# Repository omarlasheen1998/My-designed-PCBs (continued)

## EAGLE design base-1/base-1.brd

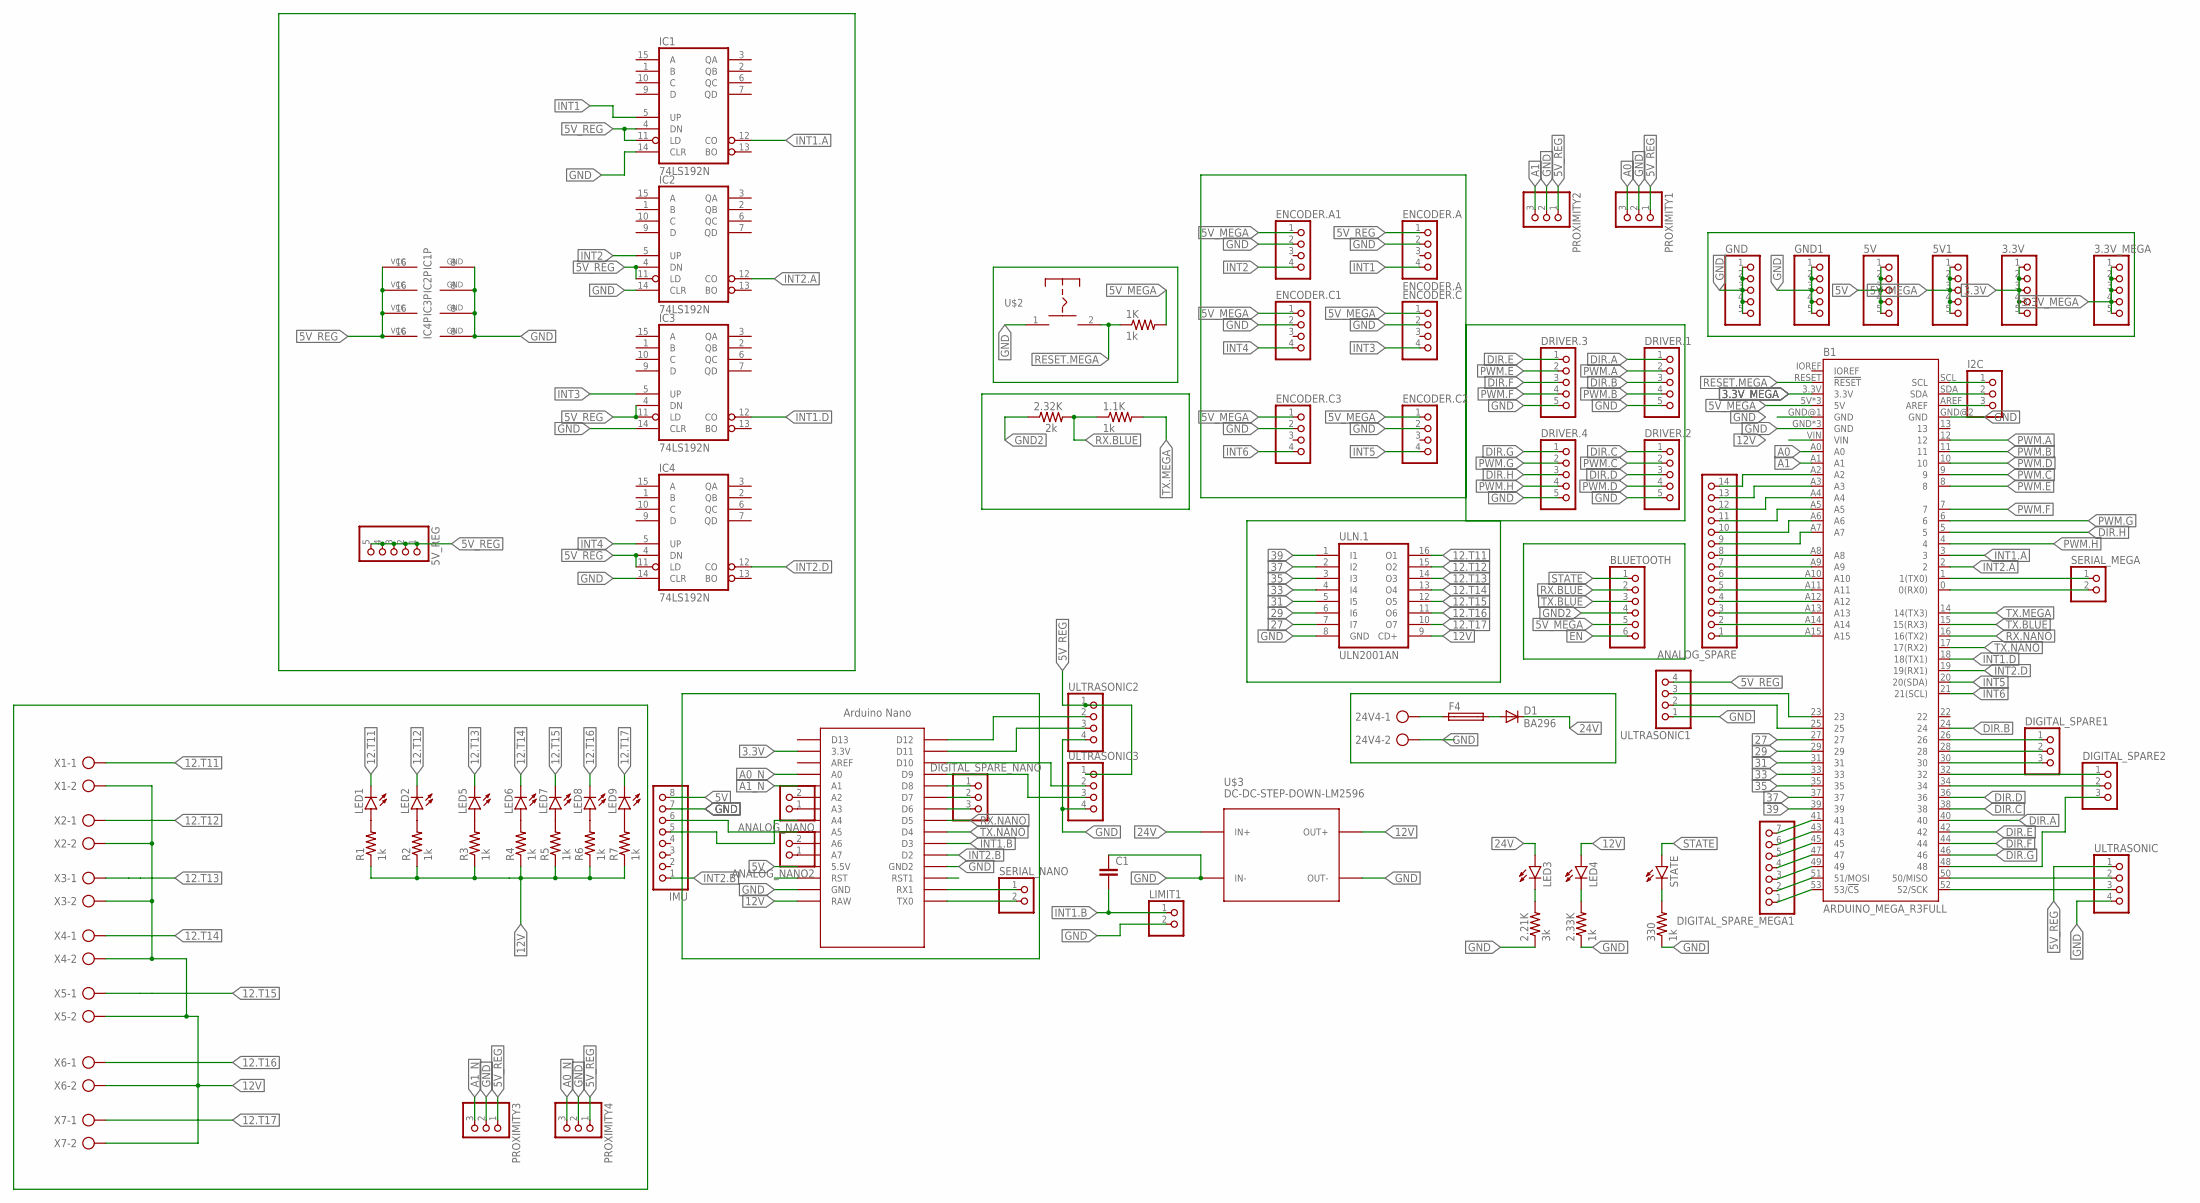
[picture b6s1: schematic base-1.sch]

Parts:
1.1K, 1K, 2.33K, 330: 1k; 0204/5
2.21K: 3k; 0207/10
2.32K: 2k; 0204/5
3.3V, 3.3V_MEGA, 5V, 5V1, 5V_REG: PINHD-1X5; 1X05
24V4: W237-113
ANALOG_NANO, ANALOG_NANO2: PINHD-1X2; 1X02
ANALOG_SPARE: PINHD-1X14; 1X14
B1: ARDUINO_MEGA_R3FULL; ARDUINO_MEGA_NO_SILK
BLUETOOTH: PINHD-1X6; 1X06
C1: C-EU025-025X050; C025-025X050
D1: BA296; P2-15
DIGITAL_SPARE1, DIGITAL_SPARE2: PINHD-1X3; 1X03
DIGITAL_SPARE_MEGA1: PINHD-1X7; 1X07
DIGITAL_SPARE_NANO: PINHD-1X3; 1X03
DRIVER.1, DRIVER.2, DRIVER.3, DRIVER.4: PINHD-1X5; 1X05
ENCODER.A: ENCODER.A; 1X04
ENCODER.A1, ENCODER.C, ENCODER.C1, ENCODER.C2, ENCODER.C3: PINHD-1X4; 1X04
F4: SH22,5A
GND, GND1: PINHD-1X5; 1X05
I2C: PINHD-1X3; 1X03
IC1, IC2, IC3, IC4: 74LS192N; DIL16
IMU: PINHD-1X8; 1X08
LED1, LED2, LED5, LED6, LED7, LED8, LED9: LED3MM
LED3, LED4: LED5MM
LIMIT1: PINHD-1X2; 1X02
PROXIMITY1, PROXIMITY2, PROXIMITY3, PROXIMITY4: PINHD-1X3; 1X03
R1, R2, R3, R4, R5, R6, R7: 1k; 0204/7
SERIAL_MEGA: PINHD-1X2; 1X02
SERIAL_NANO: PINHD-1X2; 1X02
STATE: LED3MM
U$1: NANO
U$2: PUSHBOTTON
U$3: DC-DC-STEP-DOWN-LM2596
ULN.1: ULN2001AN; DIL16
ULTRASONIC, ULTRASONIC1, ULTRASONIC2, ULTRASONIC3: PINHD-1X4; 1X04
X1, X2, X3, X4, X5, X6, X7: AK300/2

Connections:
3.3V: 3.3V.1, 3.3V.2, 3.3V.3, 3.3V.4, 3.3V.5, U$1.3.3V
3.3V_MEGA: 3.3V_MEGA.1, 3.3V_MEGA.2, 3.3V_MEGA.3, 3.3V_MEGA.4, 3.3V_MEGA.5, B1.3.3V
5V: 5V.1, 5V.2, 5V.3, 5V.4, 5V.5, IMU.8, U$1.5V (5.5V)
5V_MEGA: 1K.2, 5V1.1, 5V1.2, 5V1.3, 5V1.4, 5V1.5, B1.5V, B1.5V@1 (5V), B1.5V@2 (5V), BLUETOOTH.5, ENCODER.A1.1, ENCODER.C.1, ENCODER.C1.1, ENCODER.C2.1, ENCODER.C3.1
5V_REG: 5V_REG.1, 5V_REG.2, 5V_REG.3, 5V_REG.4, 5V_REG.5, ENCODER.A.1, IC1.4 (DN), IC1.11 (LD), IC1.16 (VCC), IC2.4 (DN), IC2.11 (LD), IC2.16 (VCC), IC3.4 (DN), IC3.11 (LD), IC3.16 (VCC), IC4.4 (DN), IC4.11 (LD), IC4.16 (VCC), PROXIMITY1.1, PROXIMITY2.1, PROXIMITY3.1, PROXIMITY4.1, ULTRASONIC.1, ULTRASONIC1.4, ULTRASONIC2.1, ULTRASONIC3.1
12.T11: LED1.K (C), ULN.1.16 (O1), X1.1
12.T12: LED2.K (C), ULN.1.15 (O2), X2.1
12.T13: LED5.K (C), ULN.1.14 (O3), X3.1
12.T14: LED6.K (C), ULN.1.13 (O4), X4.1
12.T15: LED7.K (C), ULN.1.12 (O5), X5.1
12.T16: LED8.K (C), ULN.1.11 (O6), X6.1
12.T17: LED9.K (C), ULN.1.10 (O7), X7.1
12V: B1.VIN, LED4.A, R1.1, R2.1, R3.1, R4.1, R5.1, R6.1, R7.1, U$1.RAW, U$3.OUT+, ULN.1.9 (CD+), X1.2, X2.2, X3.2, X4.2, X5.2, X6.2, X7.2
24V: D1.C, LED3.A, U$3.IN+
27: B1.27, ULN.1.7 (I7)
29: B1.29, ULN.1.6 (I6)
31: B1.31, ULN.1.5 (I5)
33: B1.33, ULN.1.4 (I4)
35: B1.35, ULN.1.3 (I3)
37: B1.37, ULN.1.2 (I2)
39: B1.39, ULN.1.1 (I1)
48: B1.48, DIGITAL_SPARE2.3
A0: B1.A0, PROXIMITY1.3
A0_N: PROXIMITY4.3, U$1.A0
A1: B1.A1, PROXIMITY2.3
A1_N: PROXIMITY3.3, U$1.A1
DIR.A: B1.40, DRIVER.1.1
DIR.B: B1.24, DRIVER.1.3
DIR.C: B1.38, DRIVER.2.1
DIR.D: B1.36, DRIVER.2.3
DIR.E: B1.42, DRIVER.3.1
DIR.F: B1.44, DRIVER.3.3
DIR.G: B1.46, DRIVER.4.1
DIR.H: B1.5, DRIVER.4.3
EN: BLUETOOTH.6
GND: 2.21K.1, 2.33K.1, 24V4.2, 330.1, B1.GND, B1.GND@1 (GND), B1.GND@2 (GND), B1.GND@3 (GND), B1.GND@4 (GND), C1.1, DRIVER.1.5, DRIVER.2.5, DRIVER.3.5, DRIVER.4.5, ENCODER.A.2, ENCODER.A1.2, ENCODER.C.2, ENCODER.C1.2, ENCODER.C2.2, ENCODER.C3.2, GND.1, GND.2, GND.3, GND.4, GND.5, GND1.1, GND1.2, GND1.3, GND1.4, GND1.5, IC1.8 (GND), IC1.14 (CLR), IC2.8 (GND), IC2.14 (CLR), IC3.8 (GND), IC3.14 (CLR), IC4.8 (GND), IC4.14 (CLR), IMU.7, LIMIT1.2, PROXIMITY1.2, PROXIMITY2.2, PROXIMITY3.2, PROXIMITY4.2, U$1.GND, U$1.GND1 (GND2), U$2.1, U$3.IN-, U$3.OUT-, ULN.1.8 (GND), ULTRASONIC.4, ULTRASONIC1.1, ULTRASONIC2.4, ULTRASONIC3.4
GND2: 2.32K.1, BLUETOOTH.4
INT1: ENCODER.A.4, IC1.5 (UP)
INT1.A: B1.3, IC1.12 (CO)
INT1.B: C1.2, LIMIT1.1, U$1.D3
INT1.D: B1.18 (18(TX1)), IC3.12 (CO)
INT2: ENCODER.A1.4, IC2.5 (UP)
INT2.A: B1.2, IC2.12 (CO)
INT2.B: IMU.1, U$1.D2
INT2.D: B1.19 (19(RX1)), IC4.12 (CO)
INT3: ENCODER.C.4, IC3.5 (UP)
INT4: ENCODER.C1.4, IC4.5 (UP)
INT5: B1.20 (20(SDA)), ENCODER.C2.4
INT6: B1.21 (21(SCL)), ENCODER.C3.4
unnamed: B1.SCL, I2C.1
unnamed: B1.SDA, I2C.2
unnamed: B1.AREF, I2C.3
unnamed: ANALOG_SPARE.1, B1.A15
unnamed: 24V4.1, F4.1
unnamed: ANALOG_SPARE.2, B1.A14
unnamed: ANALOG_SPARE.3, B1.A13
unnamed: ANALOG_SPARE.4, B1.A12
unnamed: ANALOG_SPARE.5, B1.A11
unnamed: ANALOG_SPARE.6, B1.A10
unnamed: ANALOG_SPARE.7, B1.A9
unnamed: ANALOG_SPARE.8, B1.A8
unnamed: ANALOG_SPARE.9, B1.A7
unnamed: B1.1 (1(TX0)), SERIAL_MEGA.1
unnamed: B1.0 (0(RX0)), SERIAL_MEGA.2
unnamed: 330.2, STATE.K (C)
unnamed: 2.21K.2, LED3.K (C)
unnamed: 2.33K.2, LED4.K (C)
unnamed: D1.A, F4.2
unnamed: LED1.A, R1.2
unnamed: LED2.A, R2.2
unnamed: LED5.A, R3.2
unnamed: LED6.A, R4.2
unnamed: LED7.A, R5.2
unnamed: LED8.A, R6.2
unnamed: LED9.A, R7.2
unnamed: B1.23, ULTRASONIC1.3
unnamed: B1.25, ULTRASONIC1.2
unnamed: IMU.6, U$1.A5
unnamed: IMU.5, U$1.A4
unnamed: ANALOG_NANO.1, U$1.A3
unnamed: ANALOG_NANO.2, U$1.A2
unnamed: B1.50 (50/MISO), ULTRASONIC.2
unnamed: B1.52 (52/SCK), ULTRASONIC.3
unnamed: ANALOG_NANO2.1, U$1.A7
unnamed: ANALOG_NANO2.2, U$1.A6
unnamed: B1.26, DIGITAL_SPARE1.1
unnamed: ANALOG_SPARE.10, B1.A6
unnamed: ANALOG_SPARE.11, B1.A5
unnamed: ANALOG_SPARE.12, B1.A4
unnamed: B1.28, DIGITAL_SPARE1.2
unnamed: B1.30, DIGITAL_SPARE1.3
unnamed: ANALOG_SPARE.13, B1.A3
unnamed: ANALOG_SPARE.14, B1.A2
unnamed: B1.32, DIGITAL_SPARE2.1
unnamed: B1.34, DIGITAL_SPARE2.2
unnamed: B1.41, DIGITAL_SPARE_MEGA1.7
unnamed: B1.45, DIGITAL_SPARE_MEGA1.5
unnamed: B1.43, DIGITAL_SPARE_MEGA1.6
unnamed: B1.47, DIGITAL_SPARE_MEGA1.4
unnamed: B1.49, DIGITAL_SPARE_MEGA1.3
unnamed: B1.51 (51/MOSI), DIGITAL_SPARE_MEGA1.2
unnamed: B1.53 (53/!CS), DIGITAL_SPARE_MEGA1.1
unnamed: U$1.D12, ULTRASONIC2.2
unnamed: U$1.D11, ULTRASONIC2.3
unnamed: U$1.D10, ULTRASONIC3.2
unnamed: U$1.D9, ULTRASONIC3.3
unnamed: DIGITAL_SPARE_NANO.1, U$1.D8
unnamed: DIGITAL_SPARE_NANO.2, U$1.D7
unnamed: DIGITAL_SPARE_NANO.3, U$1.D6
unnamed: SERIAL_NANO.1, U$1.RX1
unnamed: SERIAL_NANO.2, U$1.TX0
PWM.A: B1.12, DRIVER.1.2
PWM.B: B1.11, DRIVER.1.4
PWM.C: B1.9, DRIVER.2.2
PWM.D: B1.10, DRIVER.2.4
PWM.E: B1.8, DRIVER.3.2
PWM.F: B1.7, DRIVER.3.4
PWM.G: B1.6, DRIVER.4.2
PWM.H: B1.4, DRIVER.4.4
RESET.MEGA: 1K.1, B1.RESET (!RESET), U$2.2
RX.BLUE: 1.1K.1, 2.32K.2, BLUETOOTH.2
RX.NANO: B1.16 (16(TX2)), U$1.D5
STATE: BLUETOOTH.1, STATE.A
TX.BLUE: B1.15 (15(RX3)), BLUETOOTH.3
TX.MEGA: 1.1K.2, B1.14 (14(TX3))
TX.NANO: B1.17 (17(RX2)), U$1.D4

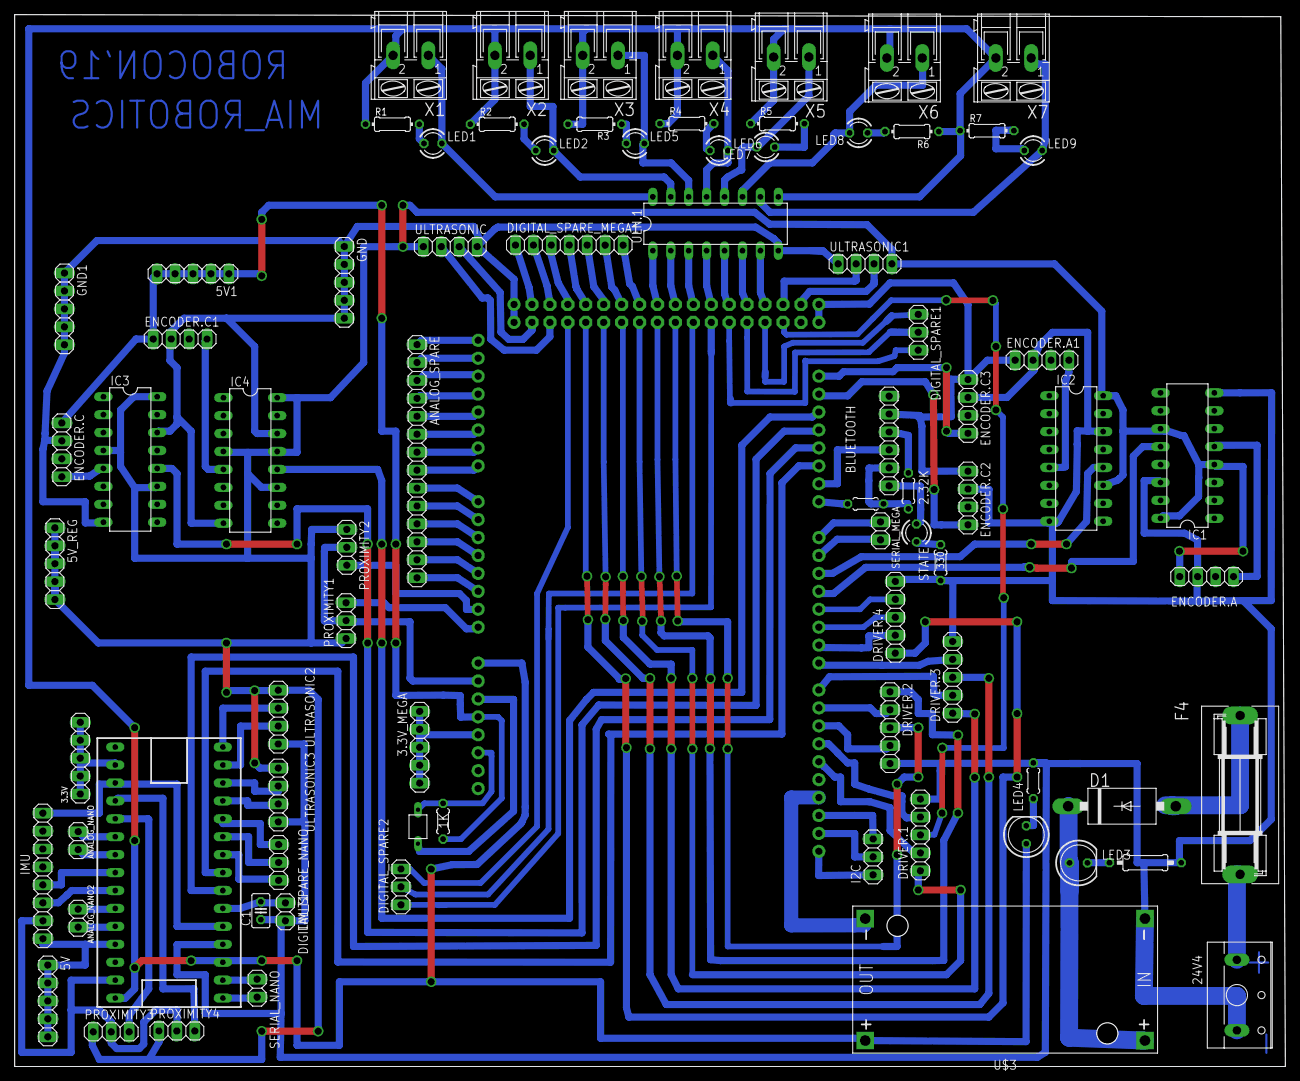
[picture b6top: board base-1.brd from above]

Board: 2 copper layers, 180.0 x 149.0 mm, 81 parts (1 on the bottom side), 125 nets.

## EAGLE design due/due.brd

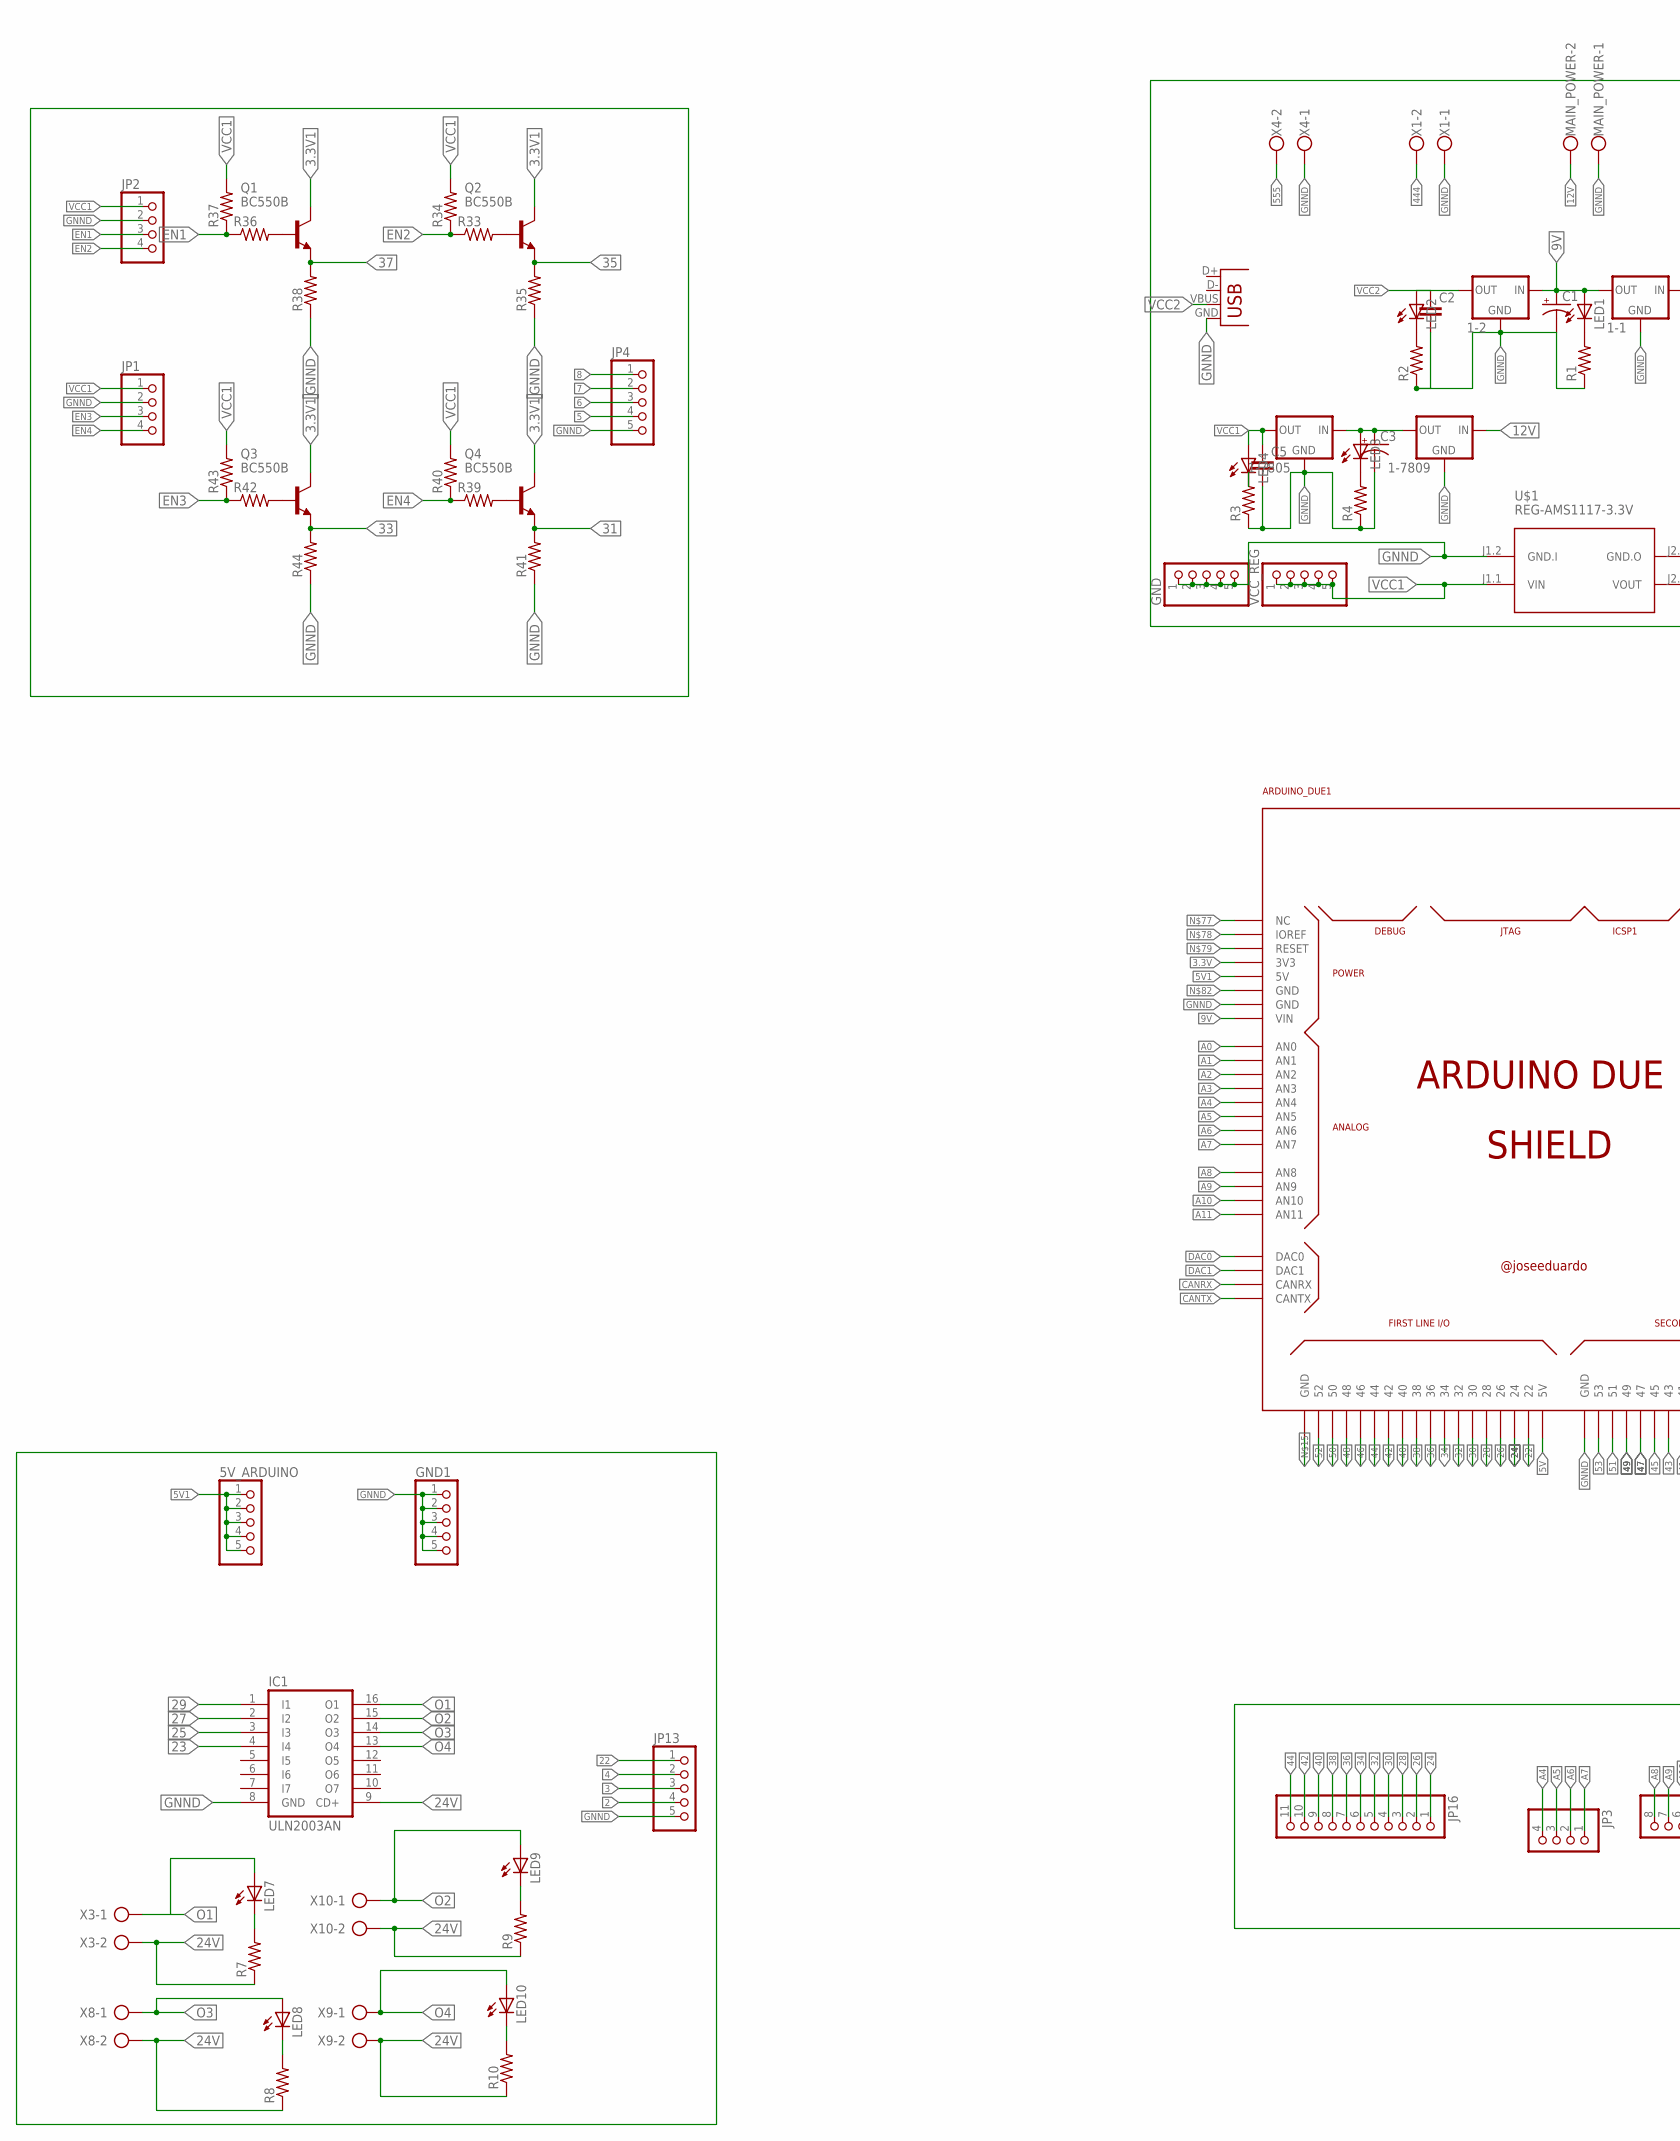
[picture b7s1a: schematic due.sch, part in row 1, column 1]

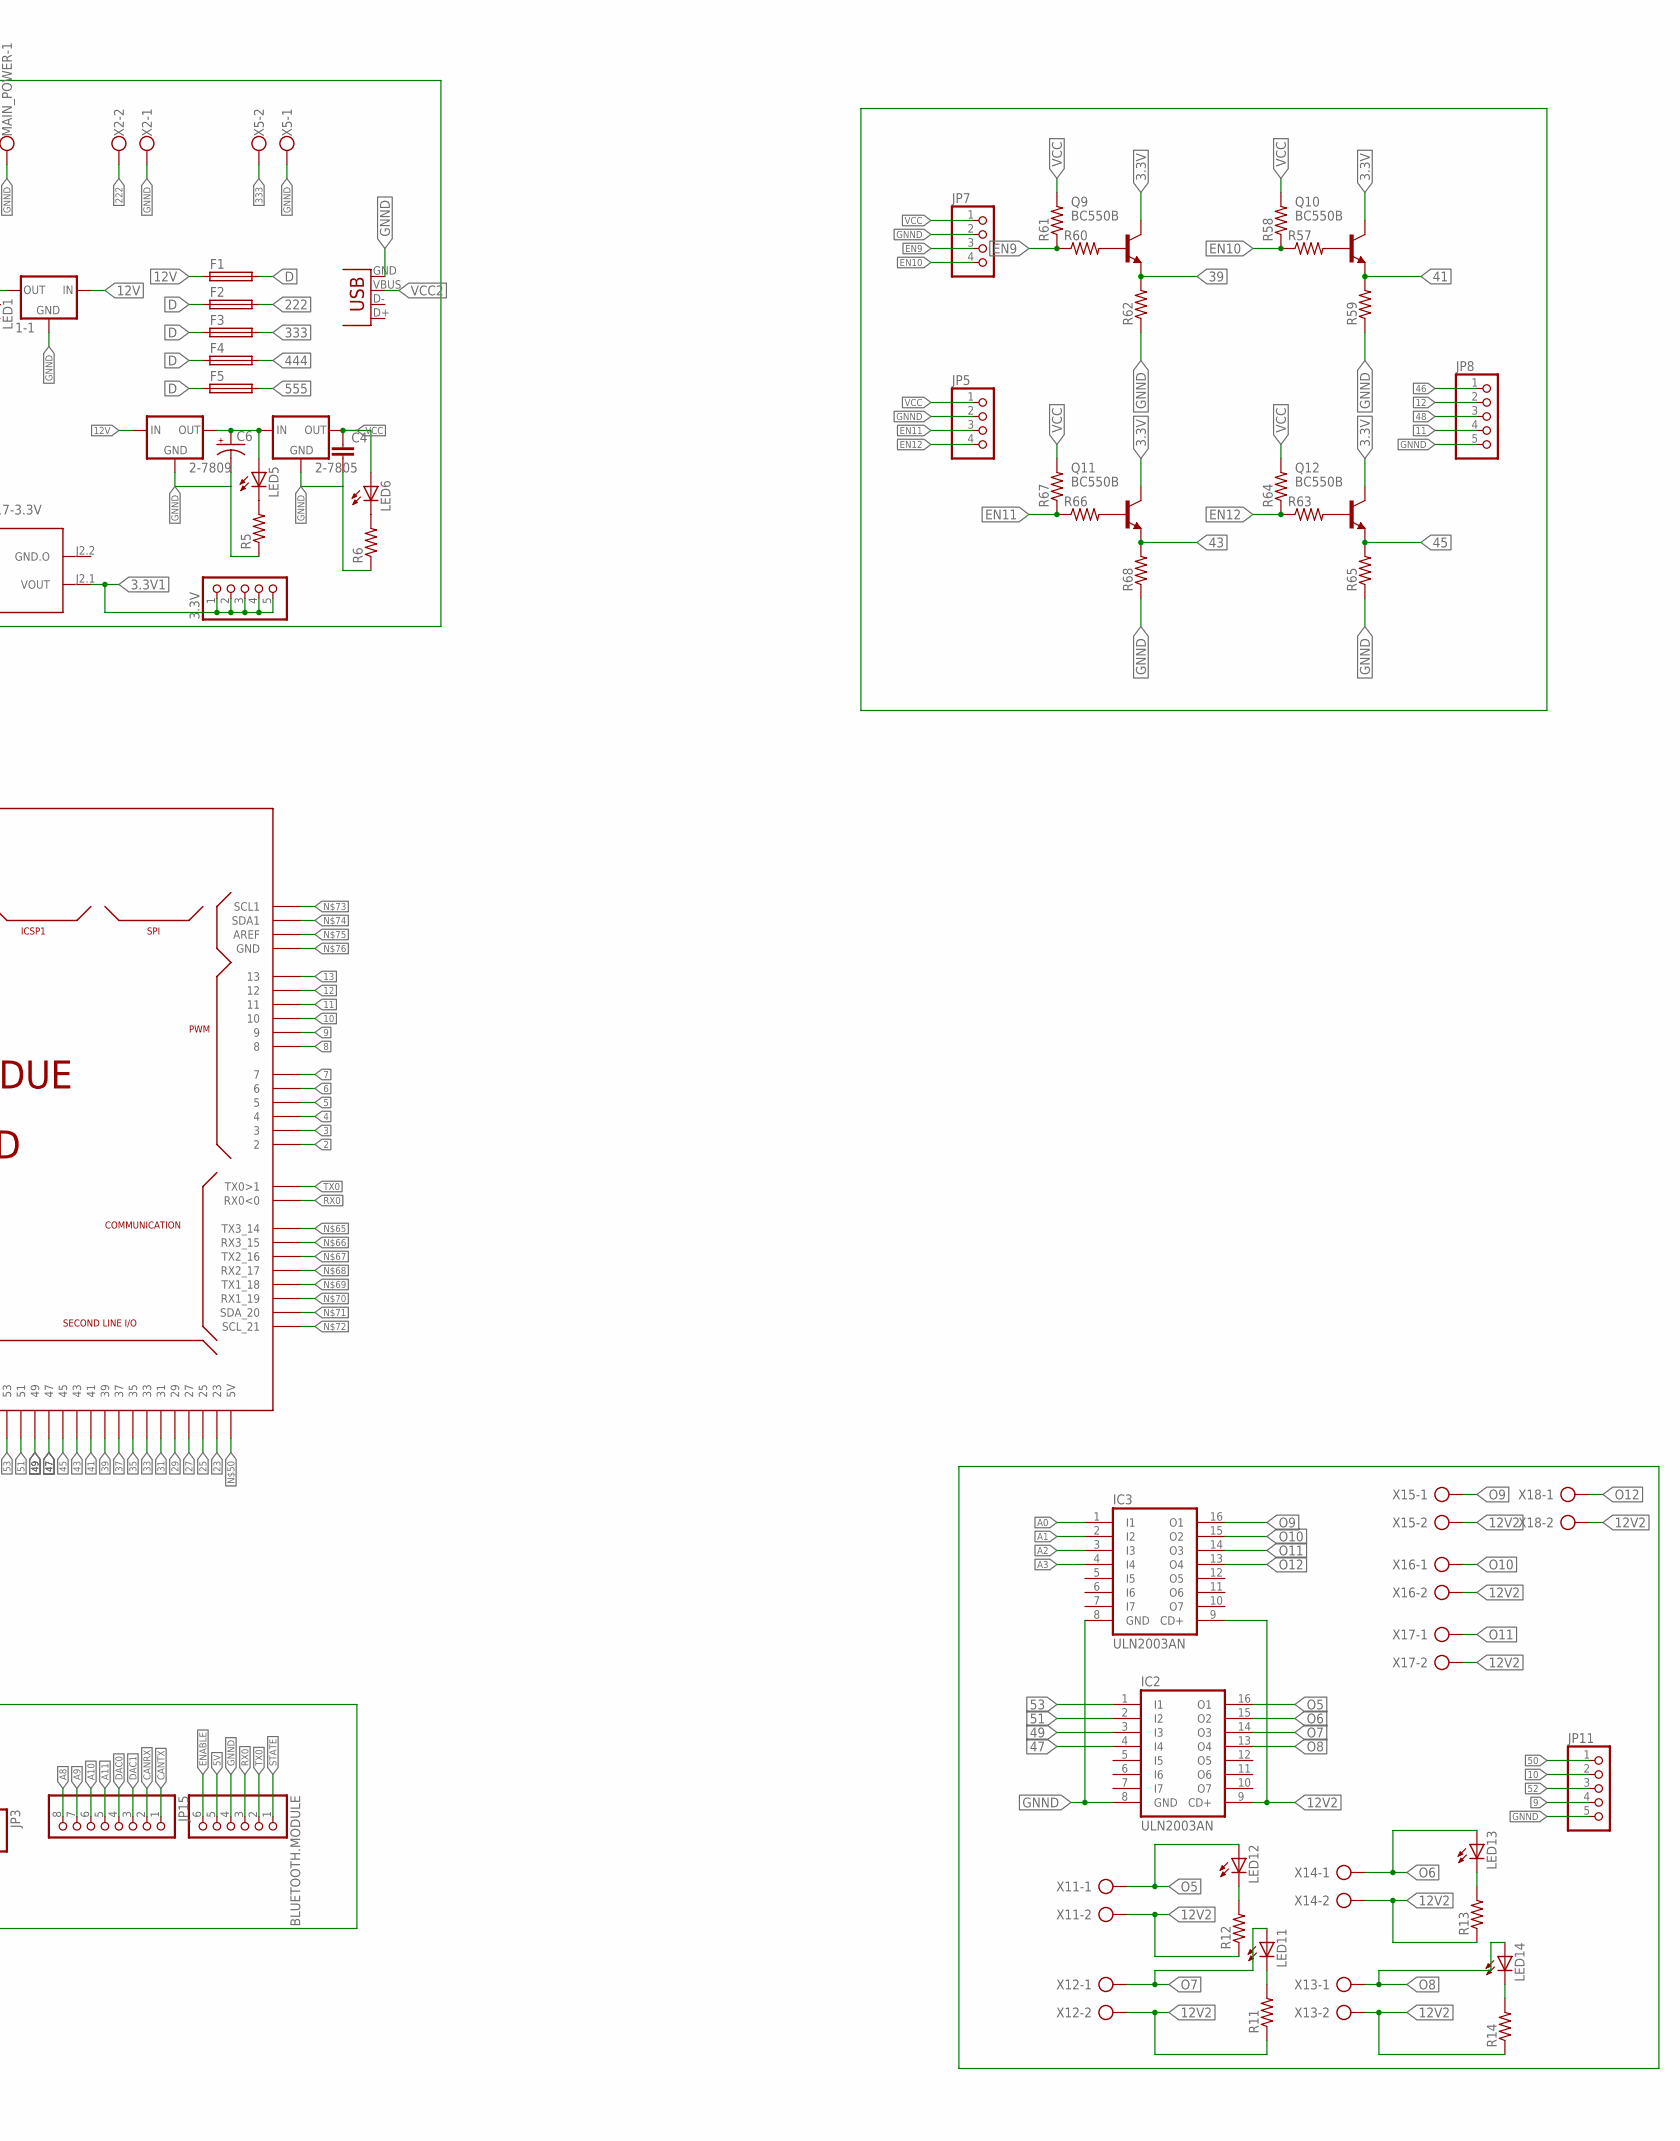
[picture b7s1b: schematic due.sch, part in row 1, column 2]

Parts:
1-1, 1-2, 1-7805, 1-7809, 2-7805, 2-7809: 78XXS
3.3V, 5V_ARDUINO: PINHD-1X5; 1X05
ARDUINO_DUE1: ARDUINO_DUE_SHIELD
BLUETOOTH.MODULE: PINHD-1X6; 1X06
C1, C3, C6: CPOL-USE2.5-7; E2,5-7
C2, C4, C5: C-EU025-025X050; C025-025X050
F1, F2, F3, F4, F5: SH22,5A
GND, GND1: PINHD-1X5; 1X05
IC1, IC2, IC3: ULN2003AN; DIL16
JP1, JP2, JP3, JP5, JP7: PINHD-1X4; 1X04
JP4, JP8, JP11, JP13: PINHD-1X5; 1X05
JP15: PINHD-1X8; 1X08
JP16: PINHD-1X11; 1X11
LED1, LED2, LED3, LED4, LED5, LED6, LED7, LED8, LED9, LED10, LED11, LED12, LED13, LED14: LED3MM
MAIN_POWER: W237-113
Q1, Q2, Q3, Q4, Q9, Q10, Q11, Q12: BC550B; TO92-EBC
R1, R5, R36, R38, R42, R44, R60, R62, R66, R68: R-US_0204/7; 0204/7
R2, R3, R4, R6, R7, R8, R9, R10, R11, R12, R13, R14, R34, R37, R40, R43, R58, R61, R64, R67: R-US_0204/5; 0204/5
R33, R35, R39, R41, R57, R59, R63, R65: R-US_0207/12; 0207/12
U$1: REG-AMS1117-3.3V; REG-AMS1117
VCC_REG: PINHD-1X5; 1X05
X1, X2, X4, X5: W237-113
X3, X8, X9, X10, X11, X12, X13, X14, X15, X16, X17, X18: AK300/2
X6, X7: USB-A-H

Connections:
2: ARDUINO_DUE1.2, JP13.4
3: ARDUINO_DUE1.3, JP13.3
3.3V: ARDUINO_DUE1.3V3, Q9.C, Q10.C, Q11.C, Q12.C
3.3V1: 3.3V.1, 3.3V.2, 3.3V.3, 3.3V.4, 3.3V.5, Q1.C, Q2.C, Q3.C, Q4.C, U$1.J2.1 (VOUT)
4: ARDUINO_DUE1.4, JP13.2
5: ARDUINO_DUE1.5, JP4.4
5V: ARDUINO_DUE1.5V0_1 (5V), BLUETOOTH.MODULE.5
5V1: 5V_ARDUINO.1, 5V_ARDUINO.2, 5V_ARDUINO.3, 5V_ARDUINO.4, 5V_ARDUINO.5, ARDUINO_DUE1.5V0 (5V)
6: ARDUINO_DUE1.6, JP4.3
7: ARDUINO_DUE1.7, JP4.2
8: ARDUINO_DUE1.8, JP4.1
9: ARDUINO_DUE1.9, JP11.4
9V: 1-1.OUT, 1-2.IN, ARDUINO_DUE1.VIN, C1.+, LED1.A
10: ARDUINO_DUE1.10, JP11.2
11: ARDUINO_DUE1.11, JP8.4
12: ARDUINO_DUE1.12, JP8.2
12V: 1-1.IN, 1-7809.IN, 2-7809.IN, F1.1, MAIN_POWER.2
12V2: IC2.9 (CD+), IC3.9 (CD+), R11.1, R12.1, R13.1, R14.1, X11.2, X12.2, X13.2, X14.2, X15.2, X16.2, X17.2, X18.2
13: ARDUINO_DUE1.13
22: ARDUINO_DUE1.22, JP13.1
23: ARDUINO_DUE1.23, IC1.4 (I4)
24: ARDUINO_DUE1.24, JP16.1
24V: IC1.9 (CD+), R7.1, R8.1, R9.1, R10.1, X3.2, X8.2, X9.2, X10.2
25: ARDUINO_DUE1.25, IC1.3 (I3)
26: ARDUINO_DUE1.26, JP16.2
27: ARDUINO_DUE1.27, IC1.2 (I2)
28: ARDUINO_DUE1.28, JP16.3
29: ARDUINO_DUE1.29, IC1.1 (I1)
30: ARDUINO_DUE1.30, JP16.4
31: ARDUINO_DUE1.31, Q4.E, R41.2
32: ARDUINO_DUE1.32, JP16.5
33: ARDUINO_DUE1.33, Q3.E, R44.2
34: ARDUINO_DUE1.34, JP16.6
35: ARDUINO_DUE1.35, Q2.E, R35.2
36: ARDUINO_DUE1.36, JP16.7
37: ARDUINO_DUE1.37, Q1.E, R38.2
38: ARDUINO_DUE1.38, JP16.8
39: ARDUINO_DUE1.39, Q9.E, R62.2
40: ARDUINO_DUE1.40, JP16.9
41: ARDUINO_DUE1.41, Q10.E, R59.2
42: ARDUINO_DUE1.42, JP16.10
43: ARDUINO_DUE1.43, Q11.E, R68.2
44: ARDUINO_DUE1.44, JP16.11
45: ARDUINO_DUE1.45, Q12.E, R65.2
46: ARDUINO_DUE1.46, JP8.1
47: ARDUINO_DUE1.47, IC2.4 (I4)
48: ARDUINO_DUE1.48, JP8.3
49: ARDUINO_DUE1.49, IC2.3 (I3)
50: ARDUINO_DUE1.50, JP11.1
51: ARDUINO_DUE1.51, IC2.2 (I2)
52: ARDUINO_DUE1.52, JP11.3
53: ARDUINO_DUE1.53, IC2.1 (I1)
222: F2.2, X2.2
333: F3.2, X5.2
444: F4.2, X1.2
555: F5.2, X4.2
A0: ARDUINO_DUE1.A0 (AN0), IC3.1 (I1)
A1: ARDUINO_DUE1.A1 (AN1), IC3.2 (I2)
A2: ARDUINO_DUE1.A2 (AN2), IC3.3 (I3)
A3: ARDUINO_DUE1.A3 (AN3), IC3.4 (I4)
A4: ARDUINO_DUE1.A4 (AN4), JP3.4
A5: ARDUINO_DUE1.A5 (AN5), JP3.3
A6: ARDUINO_DUE1.A6 (AN6), JP3.2
A7: ARDUINO_DUE1.A7 (AN7), JP3.1
A8: ARDUINO_DUE1.A8 (AN8), JP15.8
A9: ARDUINO_DUE1.A9 (AN9), JP15.7
A10: ARDUINO_DUE1.A10 (AN10), JP15.6
A11: ARDUINO_DUE1.A11 (AN11), JP15.5
CANRX: ARDUINO_DUE1.CANRX, JP15.2
CANTX: ARDUINO_DUE1.CANTX, JP15.1
D: F1.2, F2.1, F3.1, F4.1, F5.1
DAC0: ARDUINO_DUE1.DAC0, JP15.4
DAC1: ARDUINO_DUE1.DAC1, JP15.3
EN1: JP2.3, R36.1, R37.1
EN2: JP2.4, R33.1, R34.1
EN3: JP1.3, R42.1, R43.1
EN4: JP1.4, R39.1, R40.1
EN9: JP7.3, R60.1, R61.1
EN10: JP7.4, R57.1, R58.1
EN11: JP5.3, R66.1, R67.1
EN12: JP5.4, R63.1, R64.1
ENABLE: BLUETOOTH.MODULE.6
GNND: 1-1.GND, 1-2.GND, 1-7805.GND, 1-7809.GND, 2-7805.GND, 2-7809.GND, ARDUINO_DUE1.GND_1 (GND), ARDUINO_DUE1.GND_3 (GND), BLUETOOTH.MODULE.4, C1.-, C2.2, C3.-, C4.2, C5.2, C6.-, GND.1, GND.2, GND.3, GND.4, GND.5, GND1.1, GND1.2, GND1.3, GND1.4, GND1.5, IC1.8 (GND), IC2.8 (GND), IC3.8 (GND), JP1.2, JP2.2, JP4.5, JP5.2, JP7.2, JP8.5, JP11.5, JP13.5, MAIN_POWER.1, R1.1, R2.1, R3.1, R4.1, R5.1, R6.1, R35.1, R38.1, R41.1, R44.1, R59.1, R62.1, R65.1, R68.1, U$1.J1.2 (GND.I), X1.1, X2.1, X4.1, X5.1, X6.GND, X7.GND
unnamed: LED12.K (C), R12.2
unnamed: LED1.K (C), R1.2
unnamed: C2.1, LED2.A
unnamed: LED4.K (C), R3.2
unnamed: LED3.K (C), R4.2
unnamed: 2-7805.IN, 2-7809.OUT, C6.+, LED5.A
unnamed: LED2.K (C), R2.2
unnamed: LED5.K (C), R5.2
unnamed: LED6.K (C), R6.2
unnamed: LED11.K (C), R11.2
unnamed: LED13.K (C), R13.2
unnamed: LED14.K (C), R14.2
unnamed: LED10.K (C), R10.2
unnamed: LED9.K (C), R9.2
unnamed: 1-7805.IN, 1-7809.OUT, C3.+, LED3.A
unnamed: LED8.K (C), R8.2
unnamed: LED7.K (C), R7.2
unnamed: Q2.B, R33.2
unnamed: Q1.B, R36.2
unnamed: Q4.B, R39.2
unnamed: Q3.B, R42.2
unnamed: Q10.B, R57.2
unnamed: Q9.B, R60.2
unnamed: Q12.B, R63.2
unnamed: Q11.B, R66.2
O1: IC1.16 (O1), LED7.A, X3.1
O2: IC1.15 (O2), LED9.A, X10.1
O3: IC1.14 (O3), LED8.A, X8.1
O4: IC1.13 (O4), LED10.A, X9.1
O5: IC2.16 (O1), LED12.A, X11.1
O6: IC2.15 (O2), LED13.A, X14.1
O7: IC2.14 (O3), LED11.A, X12.1
O8: IC2.13 (O4), LED14.A, X13.1
O9: IC3.16 (O1), X15.1
O10: IC3.15 (O2), X16.1
O11: IC3.14 (O3), X17.1
O12: IC3.13 (O4), X18.1
RX0: ARDUINO_DUE1.0 (RX0<0), BLUETOOTH.MODULE.3
STATE: BLUETOOTH.MODULE.1
TX0: ARDUINO_DUE1.1 (TX0>1), BLUETOOTH.MODULE.2
VCC: 2-7805.OUT, C4.1, JP5.1, JP7.1, LED6.A, R58.2, R61.2, R64.2, R67.2
VCC1: 1-7805.OUT, C5.1, JP1.1, JP2.1, LED4.A, R34.2, R37.2, R40.2, R43.2, U$1.J1.1 (VIN), VCC_REG.1, VCC_REG.2, VCC_REG.3, VCC_REG.4, VCC_REG.5
VCC2: 1-2.OUT, X6.VBUS, X7.VBUS

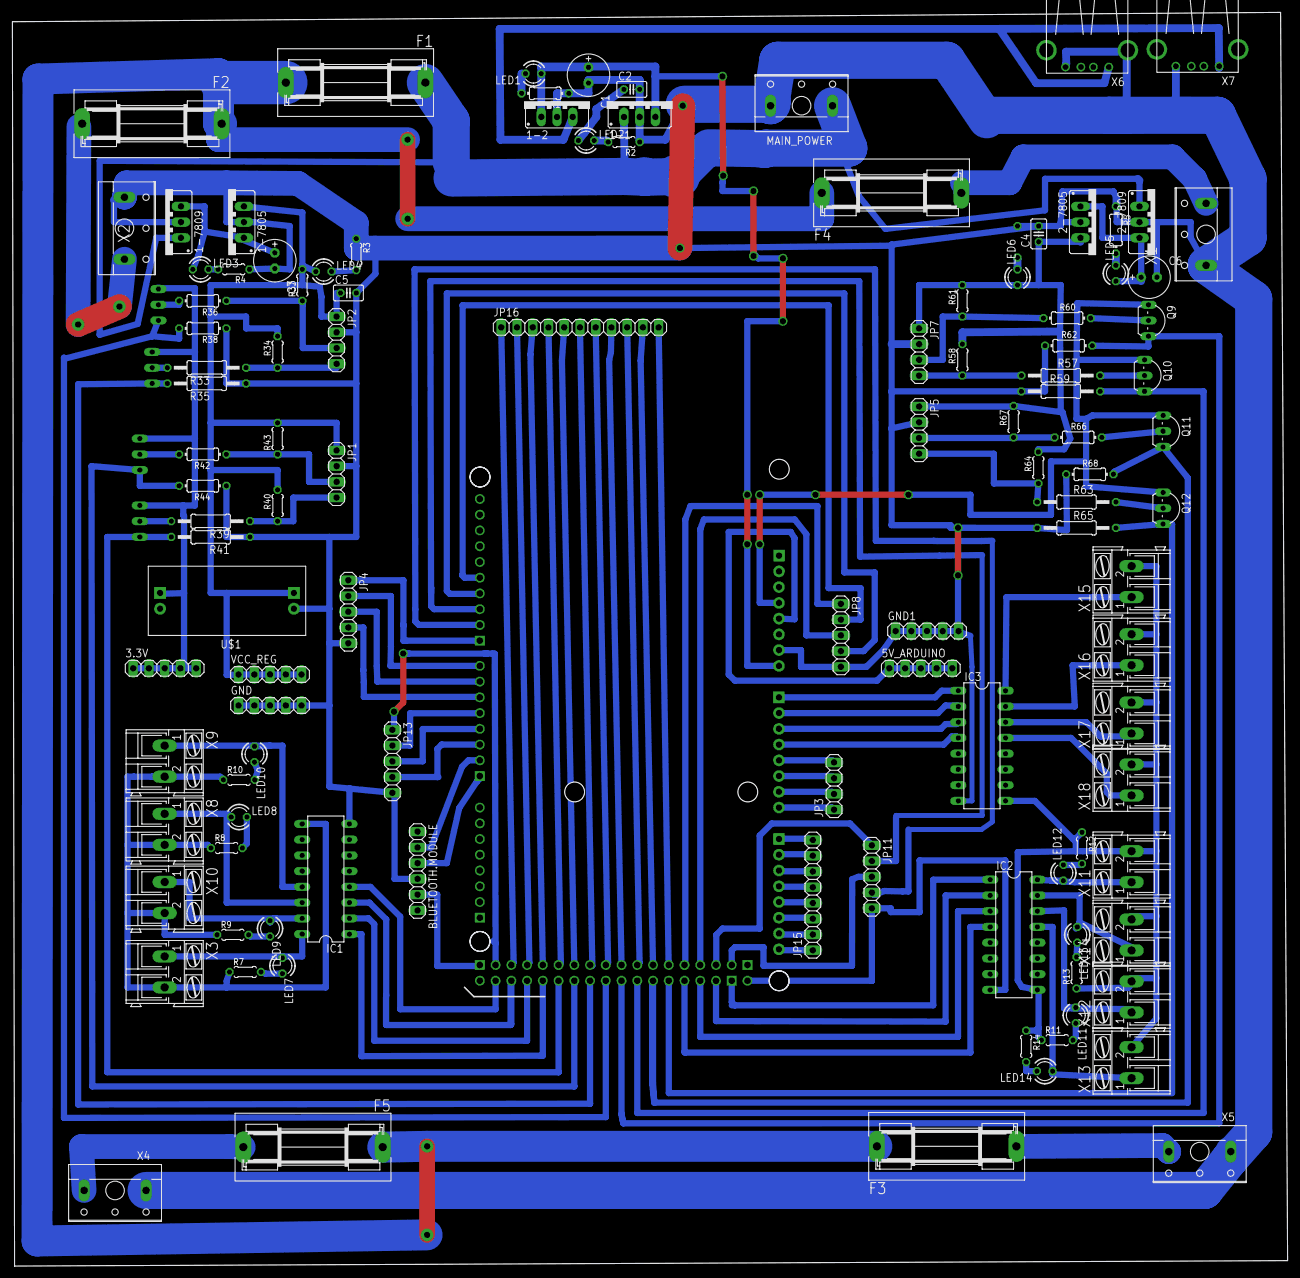
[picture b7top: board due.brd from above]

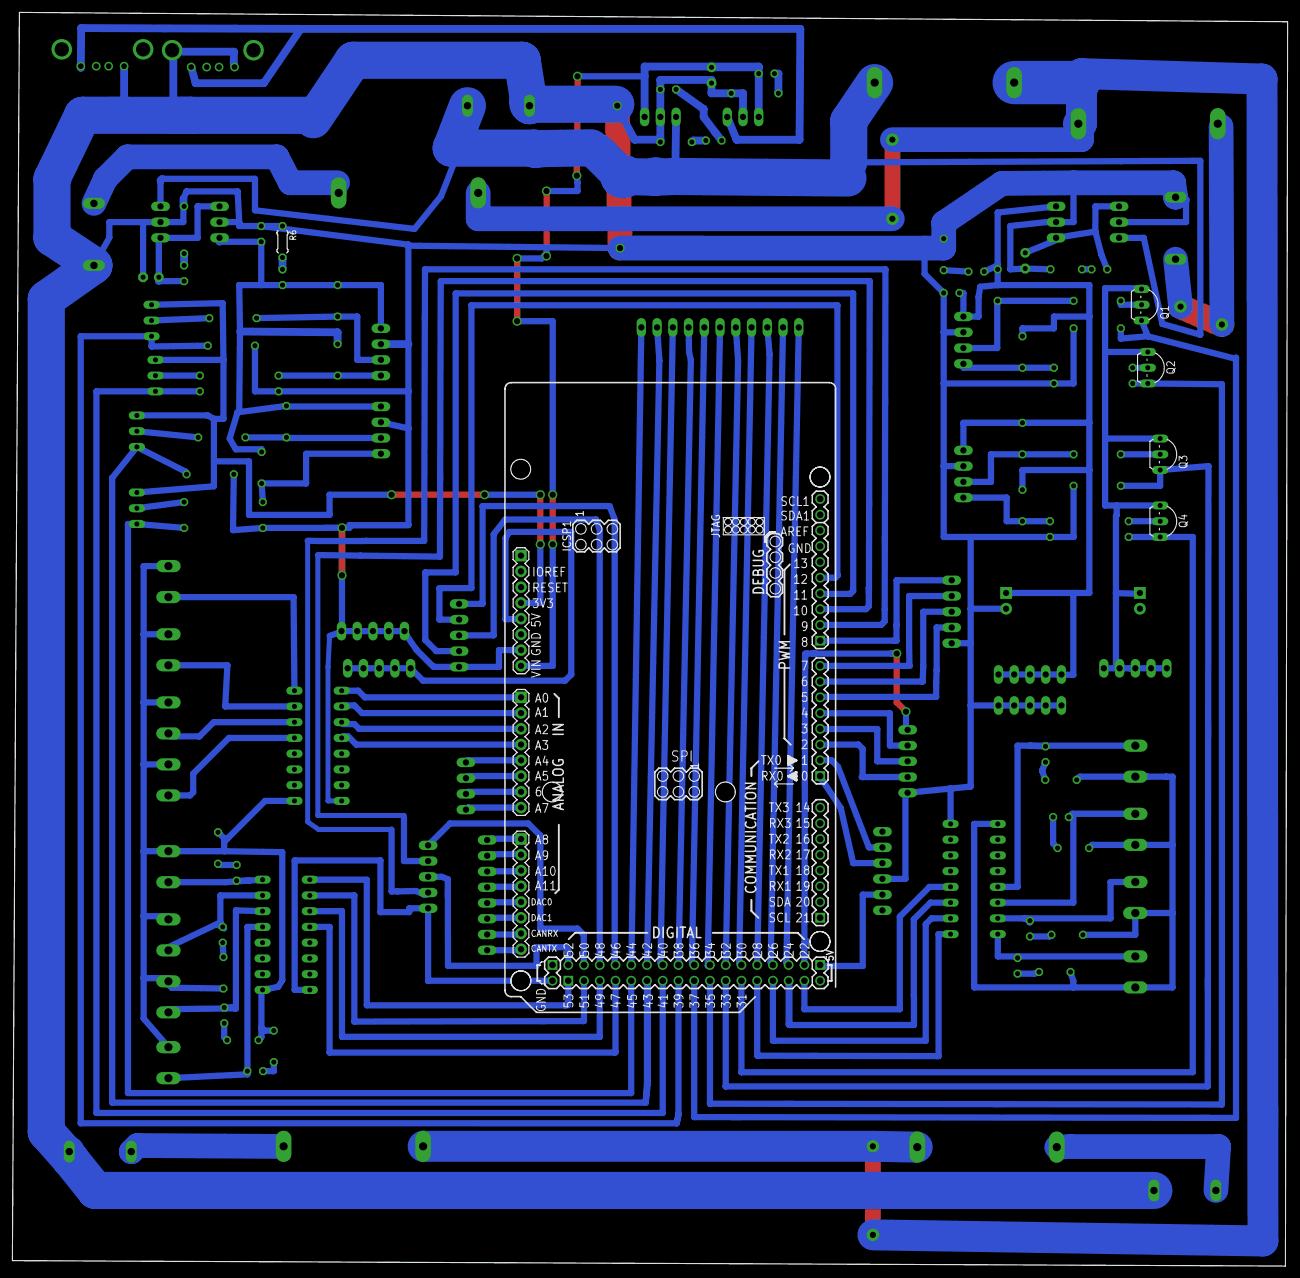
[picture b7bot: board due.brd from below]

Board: 2 copper layers, 205.7 x 202.3 mm, 118 parts (6 on the bottom side), 123 nets.
